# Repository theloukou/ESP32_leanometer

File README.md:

# ESP32 Leanometer
Motorcycle Leanometer built around ESP32 module

**WORK IN PROGRESS**

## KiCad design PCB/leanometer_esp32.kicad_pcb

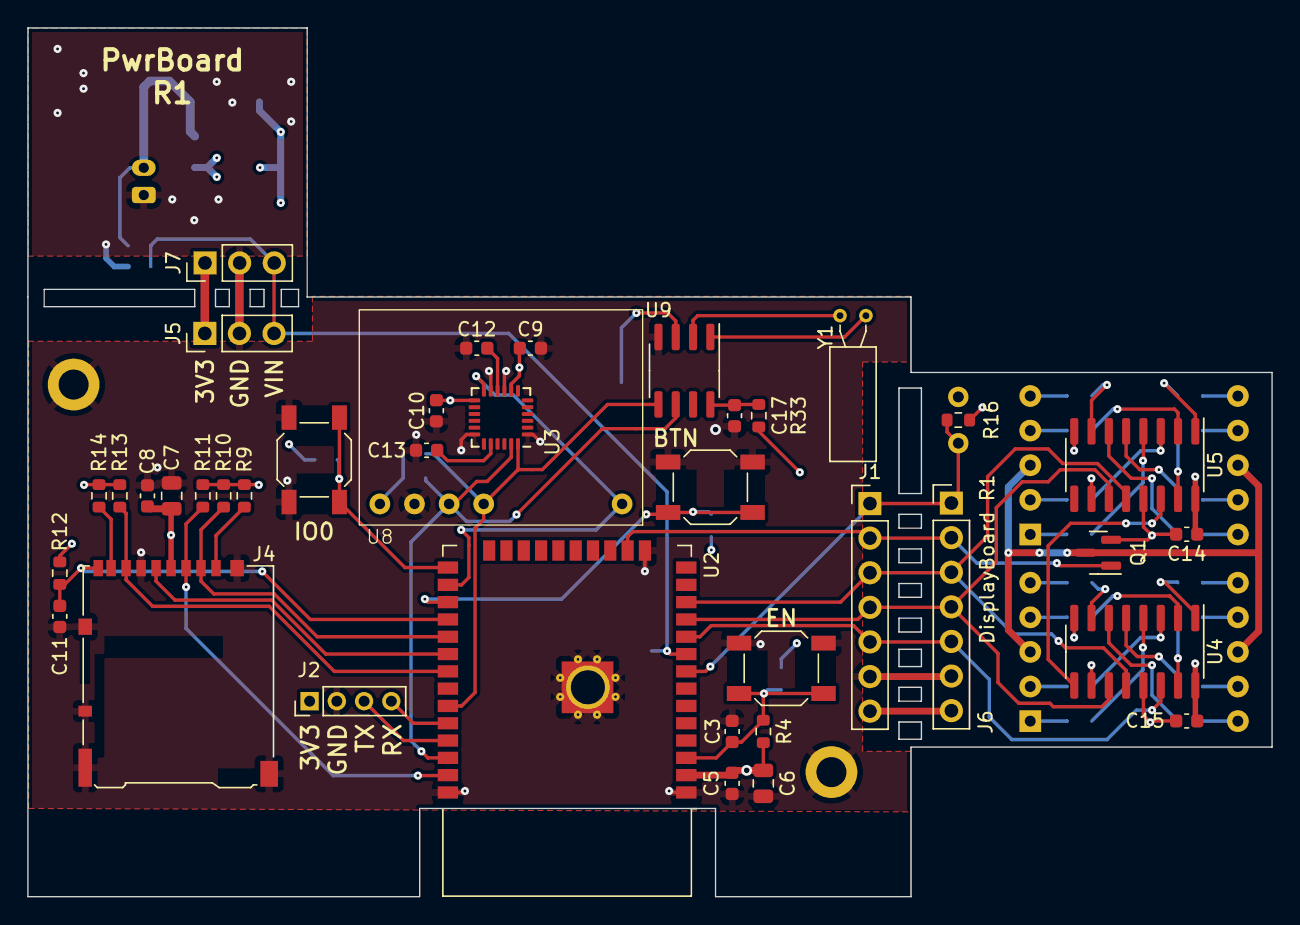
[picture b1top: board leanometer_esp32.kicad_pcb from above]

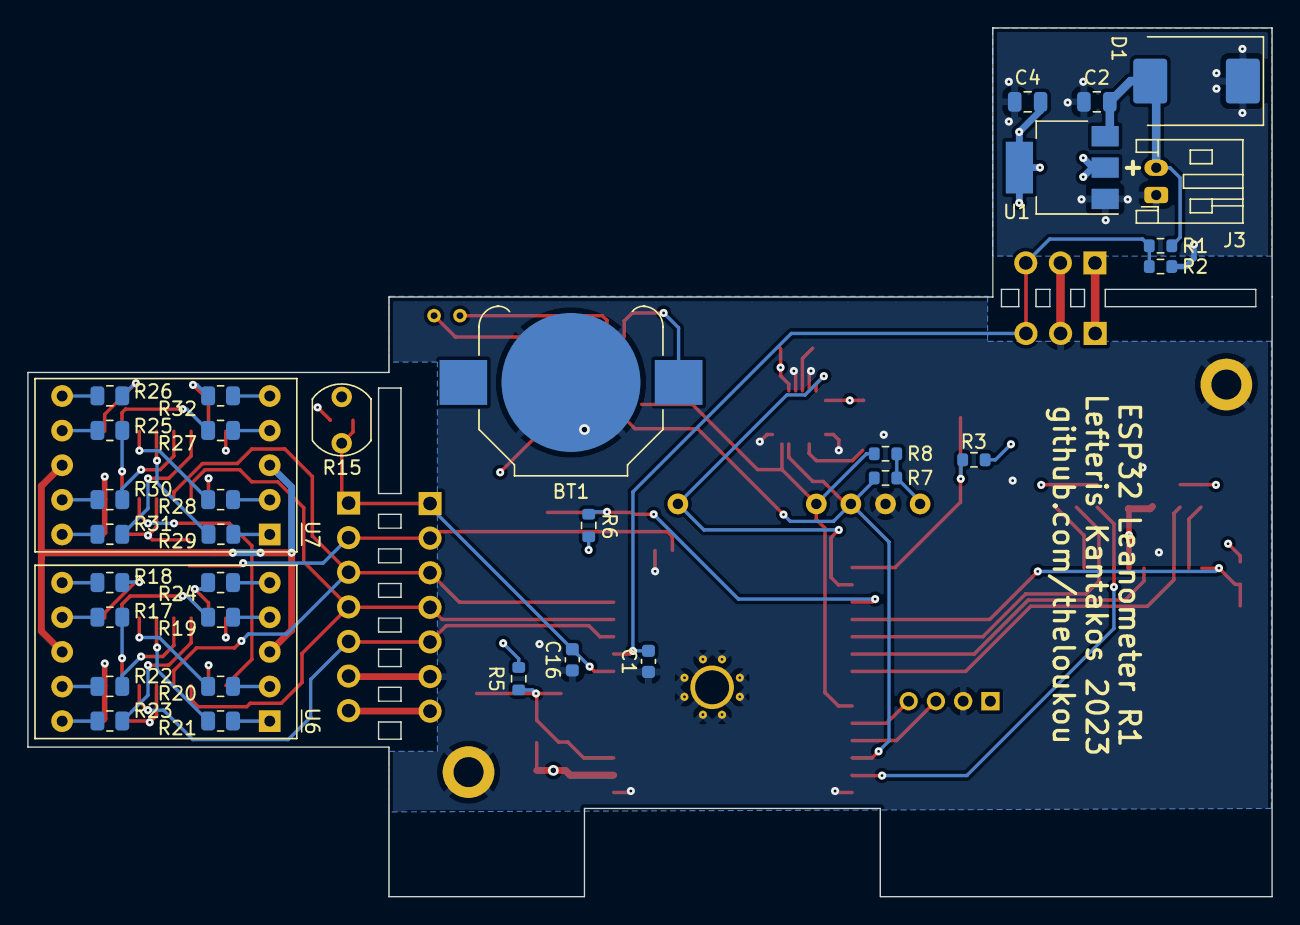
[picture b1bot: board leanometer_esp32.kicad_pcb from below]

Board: 4 copper layers, 91.3 x 63.8 mm, 75 parts (34 on the bottom side), 64 nets.

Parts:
BT1: Battery_Cell; BatteryHolder_Keystone_3000_1x12mm
C1, C3, C6, C8, C9, C10, C11, C12, C14, C15, C16, C17: 100nF; C_0603_1608Metric
C2, C4, C7: 10uF; C_0805_2012Metric
C5: 22uF; C_0805_2012Metric
C13: 2.2nF; C_0603_1608Metric
D1: SMCJ15A; D_SMC
H1, H2: MountingHole_Pad; MountingHole_2.2mm_M2_DIN965_Pad
J1, J6: Conn_01x07; PinHeader_1x07_P2.54mm_Vertical
J2: PROG; PinHeader_1x04_P2.00mm_Vertical
J3: VBAT; JST_PH_S2B-PH-K_1x02_P2.00mm_Horizontal
J4: DM3AT-SF-PEJM5; microSD_HC_Hirose_DM3AT-SF-PEJM5
J5, J7: Conn_01x03; PinHeader_1x03_P2.54mm_Vertical
Q1: BSS138; SOT-23
R1: 33K; R_0603_1608Metric
R2: 8.2K; R_0603_1608Metric
R3, R4, R5, R6, R7, R8, R9, R10, R11, R12, R13, R14, R16: 10K; R_0603_1608Metric
R15: LDR07; R_LDR_5.1x4.3mm_P3.4mm_Vertical
R17, R18, R19, R20, R21, R22, R23, R24, R25, R26, R27, R28, R29, R30, R31, R32: 100R; R_0805_2012Metric
R33: 1K; R_0603_1608Metric
SW1, SW2, SW3: SW_Push; SW_SPST_SKQG_WithStem
U1: LD1117S33TR_SOT223; SOT-223-3_TabPin2
U2: ESP32-WROOM-32D
U3: MPU-6050; InvenSense_QFN-24_4x4mm_P0.5mm
U4, U5: 74HC595; SOIC-16_3.9x9.9mm_P1.27mm
U6, U7: D168K; D1X8K
U8: GY-521; GY-521_NoSlave+AD0
U9: PCF8523; SOIC-8_3.9x4.9mm_P1.27mm
Y1: 32.768KHz; Crystal_C38-LF_D3.0mm_L8.0mm_Horizontal

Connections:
+3V3: C4.1, C5.2, C6.1, C7.1, C8.2, C9.1, C10.2, C14.1, C15.1, J1.7, J2.1, J4.4 (VDD), J5.1, J6.7, J7.1, R3.1, R4.1, R5.1, R6.1, R7.1, R8.1, R9.1, R10.1, R11.1, R12.1, R13.1, R14.1, R15.1, R33.1, U1.2 (VO), U2.2 (VDD), U3.8 (VLOGIC), U3.13 (VDD), U4.10 (~SRCLR), U4.16 (VCC), U5.10 (~SRCLR), U5.16 (VCC), U8.1 (VCC)
+BATT: C2.1, D1.2 (A2), J3.2, R1.1, U1.3 (VI)
/DisplayBoard/ADC_LDR: C16.2, J1.1, J6.1, R15.2, R16.1, U2.8 (IO32)
/DisplayBoard/DISP_BRIGHT: J1.2, J6.2, Q1.1 (G), U2.16 (IO13)
/DisplayBoard/DISP_CLOCK: J1.4, J6.4, U2.11 (IO26), U4.11 (SRCLK), U5.11 (SRCLK)
/DisplayBoard/DISP_DATA: J1.5, J6.5, U2.10 (IO25), U4.14 (SER)
/DisplayBoard/DISP_LATCH: J1.3, J6.3, U2.12 (IO27), U4.12 (RCLK), U5.12 (RCLK)
/DisplayBoard/LED_CATH: Q1.3 (D), U6.3 (CC), U6.8 (CC), U7.3 (CC), U7.8 (CC)
/DisplayBoard/SH_REG_OUT_1: U4.9 (QH'), U5.14 (SER)
/MainBoard/ADC_VBAT: C1.2, J5.3, J7.3, R1.2, R2.1, U2.9 (IO33)
/MainBoard/BUT: R6.2, SW3.1, U2.27 (IO16)
/MainBoard/EN: C3.1, R4.2, R5.2, SW2.1, U2.3 (EN)
/MainBoard/I2C_SCL: R7.2, U2.36 (IO22), U3.23 (SCL), U8.3 (SCL), U9.6 (SCL)
/MainBoard/I2C_SDA: R8.2, U2.33 (IO21), U3.24 (SDA), U8.4 (SDA), U9.5 (SDA)
/MainBoard/IMU_INT: U2.26 (IO4), U3.12 (INT), U8.8 (INT)
/MainBoard/IO0: R3.2, SW1.1, U2.25 (IO0)
/MainBoard/RX: J2.4, U2.34 (RXD0/IO3)
/MainBoard/SD_D1: J4.8 (DAT1), R14.2
/MainBoard/SD_D2: J4.1 (DAT2), R9.2
/MainBoard/SD_DET_B: C11.2, J4.9 (DET_B), R12.2, U2.28 (IO17)
/MainBoard/SD_MISO: J4.7 (DAT0), R13.2, U2.31 (IO19)
/MainBoard/SD_MOSI: J4.3 (CMD), R11.2, U2.37 (IO23)
/MainBoard/SD_SCK: J4.5 (CLK), U2.30 (IO18)
/MainBoard/SD_SS: J4.2 (DAT3/CD), R10.2, U2.29 (IO5)
/MainBoard/TX: J2.3, U2.35 (TXD0/IO1)
GND: BT1.2 (-), C1.1, C2.2, C3.2, C4.2, C5.1, C6.2, C7.2, C8.1, C9.2, C10.1, C11.1, C12.1, C13.1, C14.2, C15.2, C16.1, C17.1, D1.1 (A1), H1.1, H2.1, J1.6, J2.2, J3.1, J4.6 (VSS), J4.10 (DET_A), J4.11 (SHIELD), J5.2, J6.6, J7.2, Q1.2 (S), R2.2, R16.2, SW1.2, SW2.2, SW3.2, U1.1 (GND), U2.1 (GND), U2.15 (GND), U2.38 (GND), U2.39 (GND), U3.1 (CLKIN), U3.9 (AD0), U3.11 (FSYNC), U3.18 (GND), U4.8 (GND), U4.13 (~OE), U5.8 (GND), U5.13 (~OE), U8.2 (GND), U9.4 (VSS)
unnamed: BT1.1 (+), U9.3 (VBAT)
unnamed: C13.2, U3.20 (CPOUT)
unnamed: C12.2, U3.10 (REGOUT)
unnamed: R17.1, U4.15 (QA)
unnamed: R18.1, U4.1 (QB)
unnamed: R19.1, U4.2 (QC)
unnamed: R20.1, U4.3 (QD)
unnamed: R21.1, U4.4 (QE)
unnamed: R22.1, U4.5 (QF)
unnamed: R23.1, U4.6 (QG)
unnamed: R24.1, U4.7 (QH)
unnamed: R25.1, U5.15 (QA)
unnamed: R26.1, U5.1 (QB)
unnamed: R27.1, U5.2 (QC)
unnamed: R28.1, U5.3 (QD)
unnamed: R29.1, U5.4 (QE)
unnamed: R30.1, U5.5 (QF)
unnamed: R31.1, U5.6 (QG)
unnamed: R32.1, U5.7 (QH)
unnamed: R17.2, U6.7 (A)
unnamed: R18.2, U6.6 (B)
unnamed: R19.2, U6.4 (C)
unnamed: R20.2, U6.2 (D)
unnamed: R24.2, U6.5 (DP)
unnamed: R21.2, U6.1 (E)
unnamed: R22.2, U6.9 (F)
unnamed: R23.2, U6.10 (G)
unnamed: R25.2, U7.7 (A)
unnamed: R26.2, U7.6 (B)
unnamed: R27.2, U7.4 (C)
unnamed: R28.2, U7.2 (D)
unnamed: R32.2, U7.5 (DP)
unnamed: R29.2, U7.1 (E)
unnamed: R30.2, U7.9 (F)
unnamed: R31.2, U7.10 (G)
unnamed: U9.1 (OSCI), Y1.2
unnamed: U9.2 (OSCO), Y1.1
unnamed: C17.2, R33.2, U9.8 (VDD)

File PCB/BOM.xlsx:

ESP32 Leanometer
Component Count: | 69
Ref | Qnty | Value | Cmp name | Footprint | Description | Vendor | DNP
C1, C3, C6, C8, C9, C10, C11, C12, C14, C15, C16 | 10 | 100nF | C_Small | Capacitor_SMD:C_0603_1608Metric | Unpolarized capacitor, small symbol
C2, C4, C7 | 3 | 10uF | C_Small | Capacitor_SMD:C_0805_2012Metric | Unpolarized capacitor, small symbol
C5 | 1 | 22uF | C_Small | Capacitor_SMD:C_0805_2012Metric | Unpolarized capacitor, small symbol
C13 | 1 | 2.2nF | C_Small | Capacitor_SMD:C_0603_1608Metric | Unpolarized capacitor, small symbol
D1 | 1 | SMCJ15A | D_TVS | Diode_SMD:D_SMC | Bidirectional transient-voltage-suppression diode
H1, H2 | 2 | MountingHole_Pad | MountingHole_Pad | MountingHole:MountingHole_2.2mm_M2_DIN965_Pad | Mounting Hole with connection
J1, J6 | 2 | Conn_01x07 | Conn_01x07 | Connector_PinHeader_2.54mm:PinHeader_1x07_P2.54mm_Vertical | Generic connector, single row, 01x07, script generated (kicad-library-utils/sch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
J2 | 1 | PROG | Conn_01x04 | Connector_PinHeader_2.00mm:PinHeader_1x04_P2.00mm_Vertical | Generic connector, single row, 01x04, script generated (kicad-library-utils/sch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
J3 | 1 | VBAT | Conn_01x02 | Connector_JST:JST_PH_S2B-PH-K_1x02_P2.00mm_Horizontal | Generic connector, single row, 01x02, script generated (kicad-library-utils/sch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
J4 | 1 | DM3AT-SF-PEJM5 | Micro_SD_Card_Det2 | Connector_Card:microSD_HC_Hirose_DM3AT-SF-PEJM5 | Micro SD Card Socket with two card detection pins
J5, J7 | 2 | Conn_01x03 | Conn_01x03 | Connector_PinHeader_2.54mm:PinHeader_1x03_P2.54mm_Vertical | Generic connector, single row, 01x03, script generated (kicad-library-utils/sch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
Q1 | 1 | BSS138 | BSS138 | Package_TO_SOT_SMD:SOT-23 | 50V Vds, 0.22A Id, N-Channel MOSFET, SOT-23
R1 | 1 | 33K | R_Small_US | Resistor_SMD:R_0603_1608Metric | Resistor, small US symbol
R2 | 1 | 8.2K | R_Small_US | Resistor_SMD:R_0603_1608Metric | Resistor, small US symbol
R3, R4, R5, R6, R7, R8, R9, R10, R11, R12, R13, R14, R16 | 13 | 10K | R_Small_US | Resistor_SMD:R_0603_1608Metric | Resistor, small US symbol
R15 | 1 | LDR07 | LDR07 | OptoDevice:R_LDR_5.1x4.3mm_P3.4mm_Vertical | light dependent resistor
R17, R18, R19, R20, R21, R22, R23, R24, R25, R26, R27, R28, R29, R30, R31, R32 | 16 | 100R | R_Small_US | Resistor_SMD:R_0805_2012Metric | Resistor, small US symbol
SW1, SW2, SW3 | 3 | SW_Push | SW_Push | Button_Switch_SMD:SW_SPST_SKQG_WithStem | Push button switch, generic, two pins
U1 | 1 | LD1117S33TR_SOT223 | LD1117S33TR_SOT223 | Package_TO_SOT_SMD:SOT-223-3_TabPin2 | 800mA Fixed Low Drop Positive Voltage Regulator, Fixed Output 3.3V, SOT-223
U2 | 1 | ESP32-WROOM-32D | ESP32-WROOM-32D | RF_Module:ESP32-WROOM-32D | RF Module, ESP32-D0WD SoC, Wi-Fi 802.11b/g/n, Bluetooth, BLE, 32-bit, 2.7-3.6V,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
U3 | 1 | MPU-6050 | MPU-6050 | Sensor_Motion:InvenSense_QFN-24_4x4mm_P0.5mm | InvenSense 6-Axis Motion Sensor, Gyroscope, Accelerometer, I2C
U4, U5 | 2 | 74HC595 | 74HC595 | Package_SO:SOIC-16_3.9x9.9mm_P1.27mm | 8-bit serial in/out Shift Register 3-State Outputs
U6, U7 | 2 | D168K | D168K | Display_7Segment:D1X8K | One digit 7 segment ultra bright red LED, low current, common cathode
U8 | 1 | GY-521 | MPU6050(GY-521) | MPU6050(GY-521):GY-521_NoSlave+AD0

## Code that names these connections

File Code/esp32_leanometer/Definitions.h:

//#define SERIAL_DEBUG
#ifdef SERIAL_DEBUG
//  #define SERIAL_MPU
#endif

#define USER_BUTTON 16
#define BOOT_BUTTON 0

#define BRIGHTNESS_PIN 13
#define PWM_CHAN 0
#define PWM_FREQ 1000
#define PWM_RES 8
#define LDR 32

#define SHIFT_REG_DATA 25
#define SHIFT_REG_CLOCK 26
#define SHIFT_REG_LATCH 27

#define I2C_SDA 21
#define I2C_SCL 22
#define I2C_FREQ 400000

#define IMU_INT 4

#define VBAT_PIN 33

#define SD_MOSI 23
#define SD_MISO 19
#define SD_SCK 18
#define SD_SS 5
#define SD_DET 17

#define LDR_MIN_THRES 200
#define LDR_MAX_THRES 900
//#define CA_7SDU
#define CC_7SDU

#define PREF_NAMESPACE "Leanometer_data"
#define LOG_PATH "/logs/"
#define RESET_LOG_PATH "/resetLog.txt"

#define WIFI_SSID "Leanometer_AP"
#define WIFI_PASSWORD "1234567890"
#define WIFI_TIMEOUT 30000  //time in ms

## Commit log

2023-04-15 1st commit
2023-04-15 1st push of code and PCB files
2023-04-15 Added MPU6050 group
2023-04-16 Switched schematic to hierarchical layout, rough component placement on layout
2023-04-17 Added PowerBoard hierarchical sheet, completed layout
2023-04-17 Full layout rework
2023-04-17 Removed unused MAX_BUTTON definition
2023-04-18 Added decoupling cap on ADC_LDR signal
2023-04-18 Finalized PCB layout Added various texts Added BOM
2023-04-20 Removed a million breakaway vias for proper cutouts Cleaned up track stubs
2023-04-28 Updated gitignore
2023-04-28 Restructured PCB folder
2023-04-28 Added RTC circuit
2023-04-28 Finalized RTC layout changes
2023-04-28 Minor adjustments on PCB
2023-04-28 Added fabrication outputs, pdfs
2023-04-28 Fixed mismatched via sizes
2023-05-02 Added libs to make sure everything compiles without installing stuff by hand
2023-05-02 Removed unused EEPROM and MAX button code
2023-05-02 Libs moved to actually compile...
2023-05-02 Libs moved AGAIN
2023-05-03 Added SERIAL_DEBUG define, added SD card detection setup
2023-05-03 Initial support for G-force calculations
2023-05-03 Formatting/naming scheme fixes
2023-05-14 initial support for OTA upadates
2023-07-10 Cleaned up merging stuff
2023-07-10 Fixed button-related naming to better reflect hardware
2023-07-12 Added file basis for webUI
2023-07-13 Fixes for more reliable SD card removal
2023-07-17 Logging moves forward... Made g-force calculations available at all times for logging values Fixed SD card de-init Preliminary log file initializer
2023-07-18 Mostly logging progress Added simple incrementing naming for log filenames Added a few basic UART commands Added IMU interrupt based data reading Fixed interrupt variables into volatile
2023-07-18 Switched MPU6050 to high address to accommodate the RTC IC...
2023-07-19 Initial support for DS1307 RTC ic. Will most likely be replaced for PCF8523
2023-07-20 Switched rtc to PCF8523, added initial server code
2023-07-31 Added missing 3D models
2024-06-05 Various additions Added stuff for display flip (WIP) Added setup for webpage handlers Initial index webpage
2024-06-05 Removed unused file structure
2024-06-06 html changes. Calls setRTC function on page loading. stRTC function gets the saved date on mcu and displays it before the buttons. All requests now use fetch instead of XLM. syncRTC function now is a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
2024-06-06 Updated endpoints, added server functionality
2024-06-06 Update getRTC function to receive Date in timestamp form and return it in 'human
2024-06-06 Changed unit time tag to unixTime. Also added the calibration function.
2024-06-06 Added calibration server handler Added date field again on HTML Removed calibration JS function (breaks C compile?)
2024-06-07 Added id in p element. Async all functions. timestamp to date needs testing.
2024-06-07 HTML page now lives in PROGMEM instead of SPIFFS IMU cal trigger from webpage Fixed RETARDED JS error, fixed timestamp decoding
2024-06-13 Minor adjustments in library inclusion order
2024-06-13 Added lib brouping descriptions
2024-06-20 Refactored display update procces Added battery voltage display on boot
2024-06-21 Added display brightness adjustment on startup Fixes #10
2024-06-21 Added reset reason logging to SD if present Minor changes in SD handling to accomodate reset reason logging
2024-06-24 Server/WIFI now turn off after 30sec with no client. Switched OTA to newer library version
